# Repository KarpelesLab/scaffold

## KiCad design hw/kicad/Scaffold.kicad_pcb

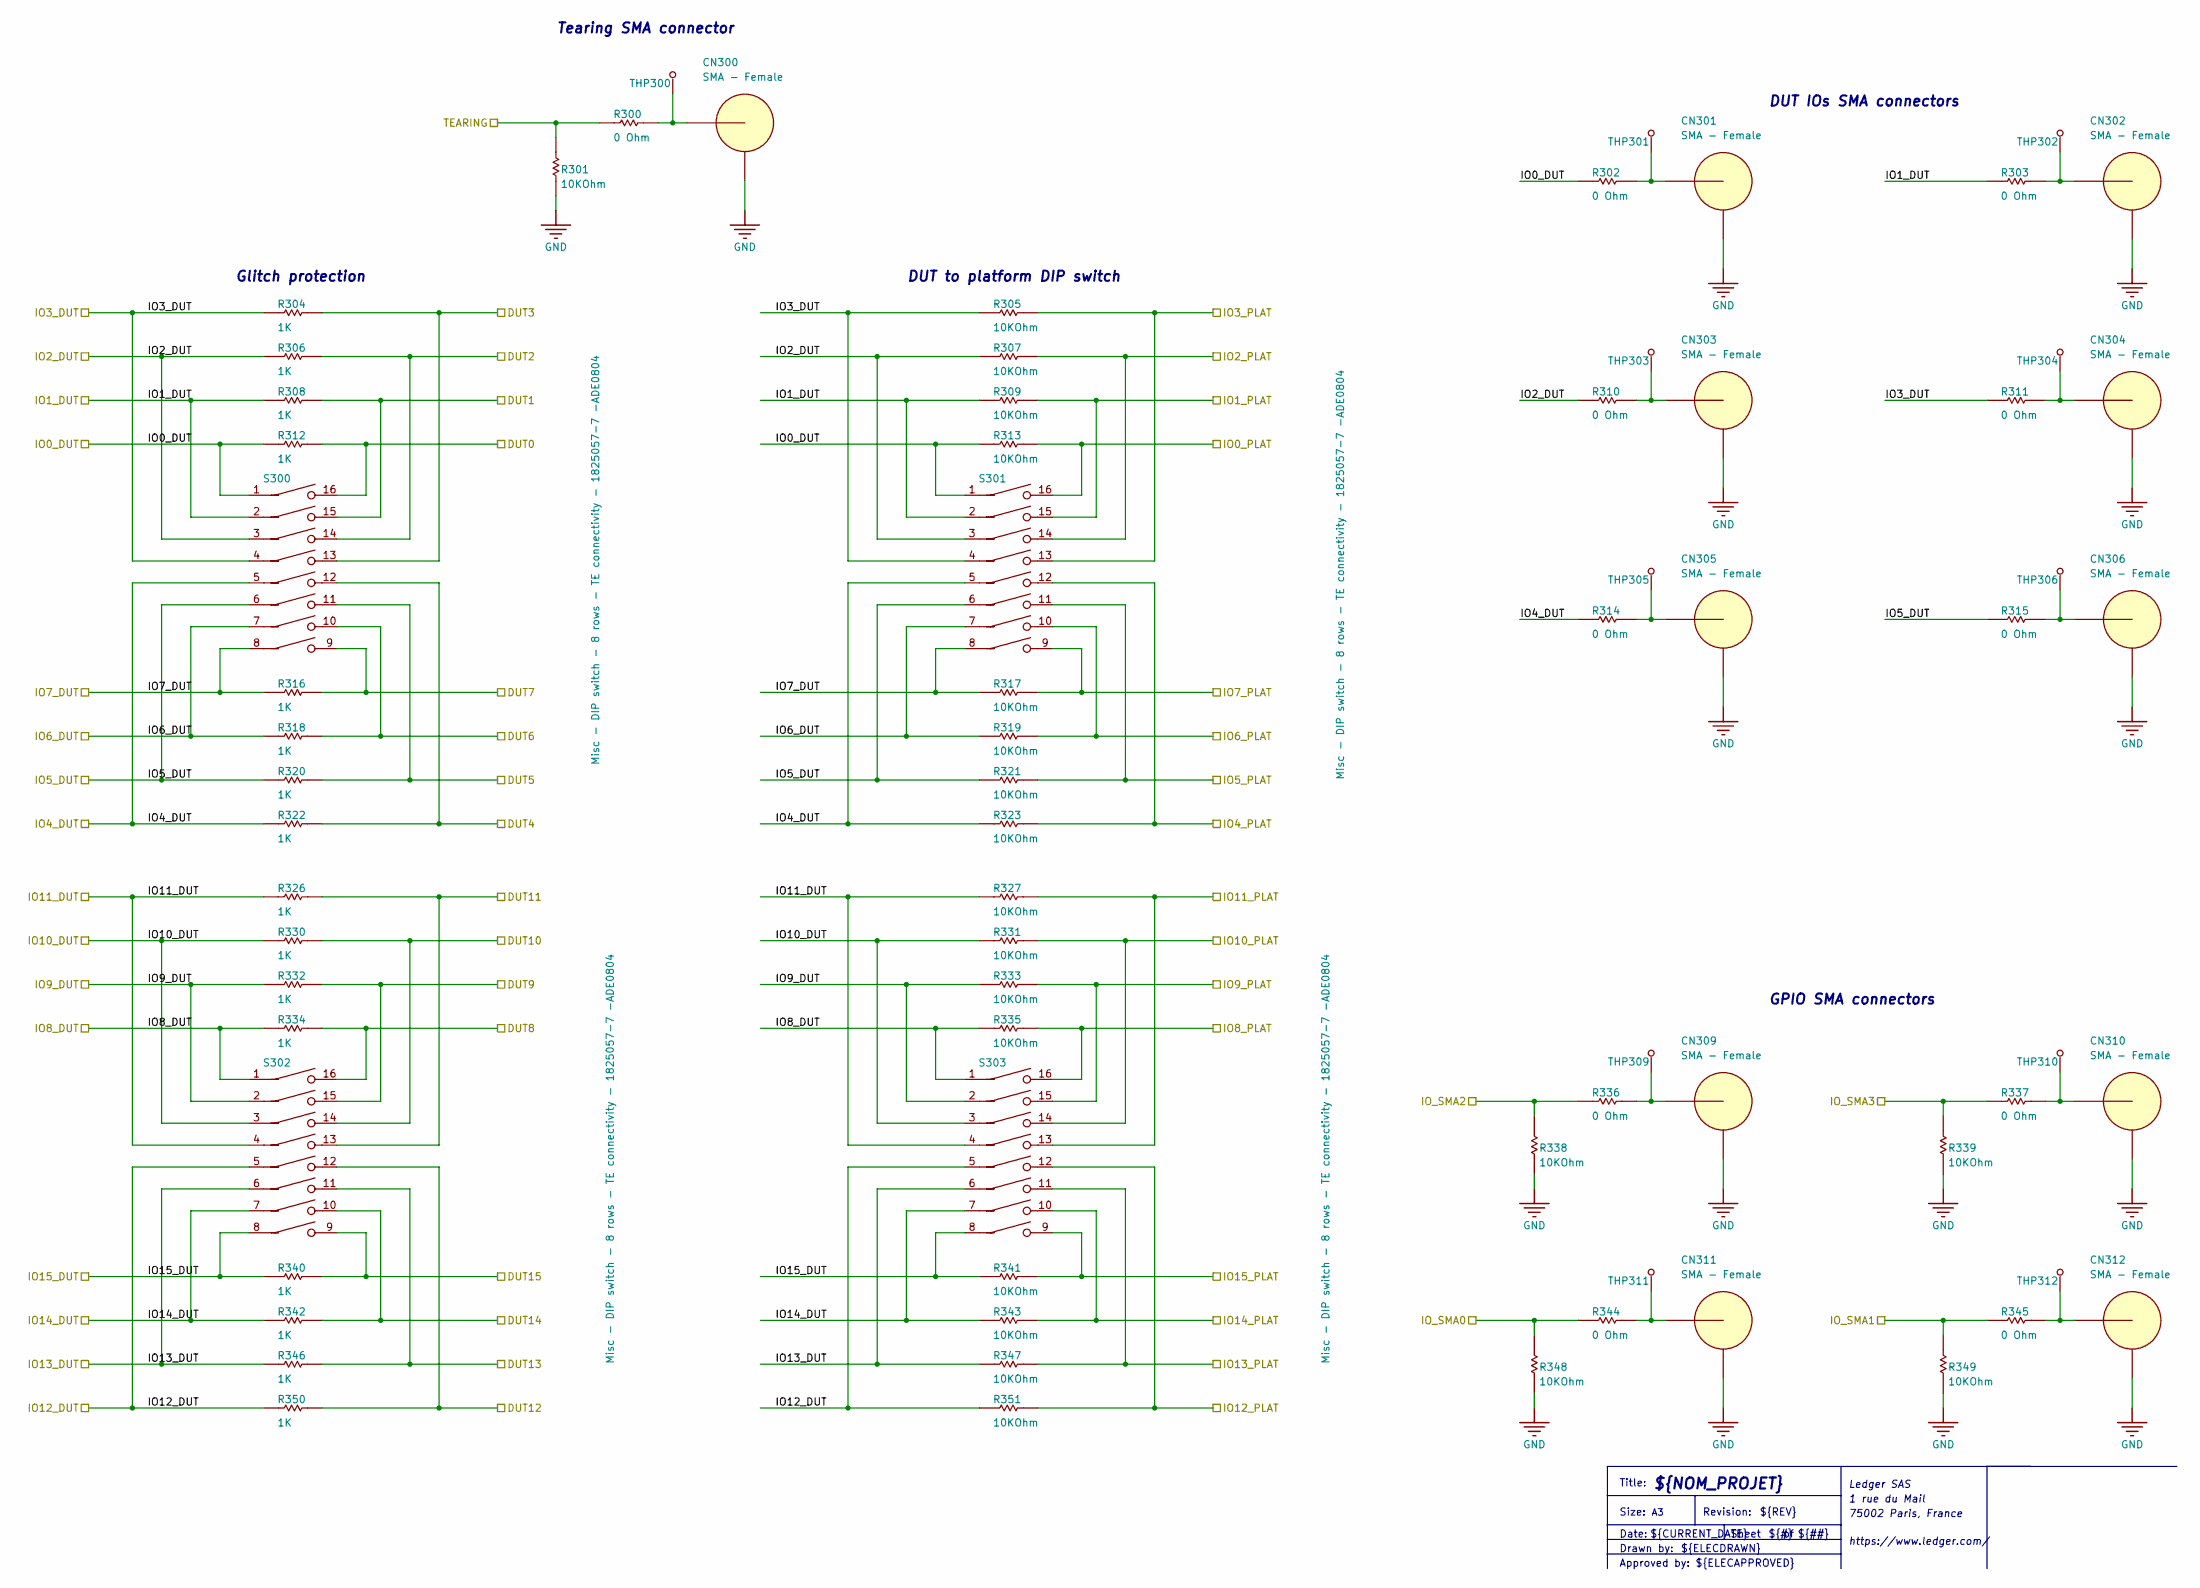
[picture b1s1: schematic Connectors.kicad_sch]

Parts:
CN300, CN301, CN302, CN303, CN304, CN305, CN306, CN309, CN310, CN311, CN312: SMA - Female; SAMTEC_SMA-J-P-X-ST-EM3; MANUFACTURER PN SMA–J–P–H–ST–EM3
R300, R302, R303, R310, R311, R314, R315, R336, R337, R344, R345: 0 Ohm; RES0603; TOLERANCE 1%; MANUFACTURER PN CRCW06030000FKEA
R301, R305, R307, R309, R313, R317, R319, R321, R323, R327, R331, R333, R335, R338, R339, R341, R343, R347, R348, R349, R351: 10KOhm; RES0603; TOLERANCE 1%; MANUFACTURER PN RC0603FR-0710KL
R304, R306, R308, R312, R316, R318, R320, R322, R326, R330, R332, R334, R340, R342, R346, R350: 1K; RES0603; TOLERANCE 1%; MANUFACTURER PN RC0603FR-071KL
S300, S301, S302, S303: Misc - DIP switch - 8 rows - TE connectivity - 18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; SWDIP16_300X3.51; MANUFACTURER PN1 ADE0804
THP300, THP301, THP302, THP303, THP304, THP305, THP306, THP309, THP310, THP311, THP312: Misc - Test pin - Through hole - Millmax - 6821-0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; MILLMAX_6821-0-00-15-00-00-08-0; MANUFACTURER PN 6821-0-00-15-00-00-08-0

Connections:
/DUT_D0: R312.2, S300.16; also elsewhere on the board
/DUT_D1: R308.2, S300.15; also elsewhere on the board
/DUT_D2: R306.2, S300.14; also elsewhere on the board
/U_Connectors/DUT3: R304.2, S300.13; also elsewhere on the board
/U_Connectors/DUT4: R322.2, S300.12; also elsewhere on the board
/U_Connectors/DUT5: R320.2, S300.11; also elsewhere on the board
/U_Connectors/DUT6: R318.2, S300.10; also elsewhere on the board
/U_Connectors/DUT7: R316.2, S300.9; also elsewhere on the board
/U_Connectors/DUT8: R334.2, S302.16; also elsewhere on the board
/U_Connectors/DUT9: R332.2, S302.15; also elsewhere on the board
/U_Connectors/DUT10: R330.2, S302.14; also elsewhere on the board
/U_Connectors/DUT11: R326.2, S302.13; also elsewhere on the board
/U_Connectors/DUT12: R350.2, S302.12; also elsewhere on the board
/U_Connectors/DUT13: R346.2, S302.11; also elsewhere on the board
/U_Connectors/DUT14: R342.2, S302.10; also elsewhere on the board
/U_Connectors/DUT15: R340.2, S302.9; also elsewhere on the board
/U_Connectors/IO0_DUT: R302.1, R312.1, R313.1, S300.1, S301.1; also elsewhere on the board
/U_Connectors/IO0_PLAT: R313.2, S301.16; also elsewhere on the board
/U_Connectors/IO1_DUT: R303.1, R308.1, R309.1, S300.2, S301.2; also elsewhere on the board
/U_Connectors/IO1_PLAT: R309.2, S301.15; also elsewhere on the board
/U_Connectors/IO2_DUT: R306.1, R307.1, R310.1, S300.3, S301.3; also elsewhere on the board
/U_Connectors/IO2_PLAT: R307.2, S301.14; also elsewhere on the board
/U_Connectors/IO3_DUT: R304.1, R305.1, R311.1, S300.4, S301.4; also elsewhere on the board
/U_Connectors/IO3_PLAT: R305.2, S301.13; also elsewhere on the board
/U_Connectors/IO4_DUT: R314.1, R322.1, R323.1, S300.5, S301.5; also elsewhere on the board
/U_Connectors/IO4_PLAT: R323.2, S301.12; also elsewhere on the board
/U_Connectors/IO5_DUT: R315.1, R320.1, R321.1, S300.6, S301.6; also elsewhere on the board
/U_Connectors/IO5_PLAT: R321.2, S301.11; also elsewhere on the board
/U_Connectors/IO6_DUT: R318.1, R319.1, S300.7, S301.7; also elsewhere on the board
/U_Connectors/IO6_PLAT: R319.2, S301.10; also elsewhere on the board
/U_Connectors/IO7_DUT: R316.1, R317.1, S300.8, S301.8; also elsewhere on the board
/U_Connectors/IO7_PLAT: R317.2, S301.9; also elsewhere on the board
/U_Connectors/IO8_DUT: R334.1, R335.1, S302.1, S303.1; also elsewhere on the board
/U_Connectors/IO8_PLAT: R335.2, S303.16; also elsewhere on the board
/U_Connectors/IO9_DUT: R332.1, R333.1, S302.2, S303.2; also elsewhere on the board
/U_Connectors/IO9_PLAT: R333.2, S303.15; also elsewhere on the board
/U_Connectors/IO10_DUT: R330.1, R331.1, S302.3, S303.3; also elsewhere on the board
/U_Connectors/IO10_PLAT: R331.2, S303.14; also elsewhere on the board
/U_Connectors/IO11_DUT: R326.1, R327.1, S302.4, S303.4; also elsewhere on the board
/U_Connectors/IO11_PLAT: R327.2, S303.13; also elsewhere on the board
/U_Connectors/IO12_DUT: R350.1, R351.1, S302.5, S303.5; also elsewhere on the board
/U_Connectors/IO12_PLAT: R351.2, S303.12; also elsewhere on the board
/U_Connectors/IO13_DUT: R346.1, R347.1, S302.6, S303.6; also elsewhere on the board
/U_Connectors/IO13_PLAT: R347.2, S303.11; also elsewhere on the board
/U_Connectors/IO14_DUT: R342.1, R343.1, S302.7, S303.7; also elsewhere on the board
/U_Connectors/IO14_PLAT: R343.2, S303.10; also elsewhere on the board
/U_Connectors/IO15_DUT: R340.1, R341.1, S302.8, S303.8; also elsewhere on the board
/U_Connectors/IO15_PLAT: R341.2, S303.9; also elsewhere on the board
/U_Connectors/IO_SMA0: R344.1, R348.2; also elsewhere on the board
/U_Connectors/IO_SMA1: R345.1, R349.2; also elsewhere on the board
/U_Connectors/IO_SMA2: R336.1, R338.2; also elsewhere on the board
/U_Connectors/IO_SMA3: R337.1, R339.2; also elsewhere on the board
/U_Connectors/TEARING: R300.1, R301.2; also elsewhere on the board
GND: CN300.2, CN300.3, CN301.2, CN301.3, CN302.2, CN302.3, CN303.2, CN303.3, CN304.2, CN304.3, CN305.2, CN305.3, CN306.2, CN306.3, CN309.2, CN309.3, CN310.2, CN310.3, CN311.2, CN311.3, CN312.2, CN312.3, R301.1, R338.1, R339.1, R348.1, R349.1; also elsewhere on the board
unnamed: CN300.1, R300.2, THP300.1
unnamed: CN301.1, R302.2, THP301.1
unnamed: CN302.1, R303.2, THP302.1
unnamed: CN303.1, R310.2, THP303.1
unnamed: CN304.1, R311.2, THP304.1
unnamed: CN305.1, R314.2, THP305.1
unnamed: CN306.1, R315.2, THP306.1
unnamed: CN309.1, R336.2, THP309.1
unnamed: CN310.1, R337.2, THP310.1
unnamed: CN311.1, R344.2, THP311.1
unnamed: CN312.1, R345.2, THP312.1

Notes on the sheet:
Sheet
DUT IOs SMA connectors
Drawn by:
Tearing SMA connector
GPIO SMA connectors
Glitch protection
${ELECDRAWN}
Ledger SAS
${REV}
${CURRENT_DATE}
https://www.ledger.com/
Revision:
Title:
1 rue du Mail
Approved by:
DUT to platform DIP switch
${NOM_PROJET}
Size:
${##}
Date:
${#}
${ELECAPPROVED}
75002 Paris, France

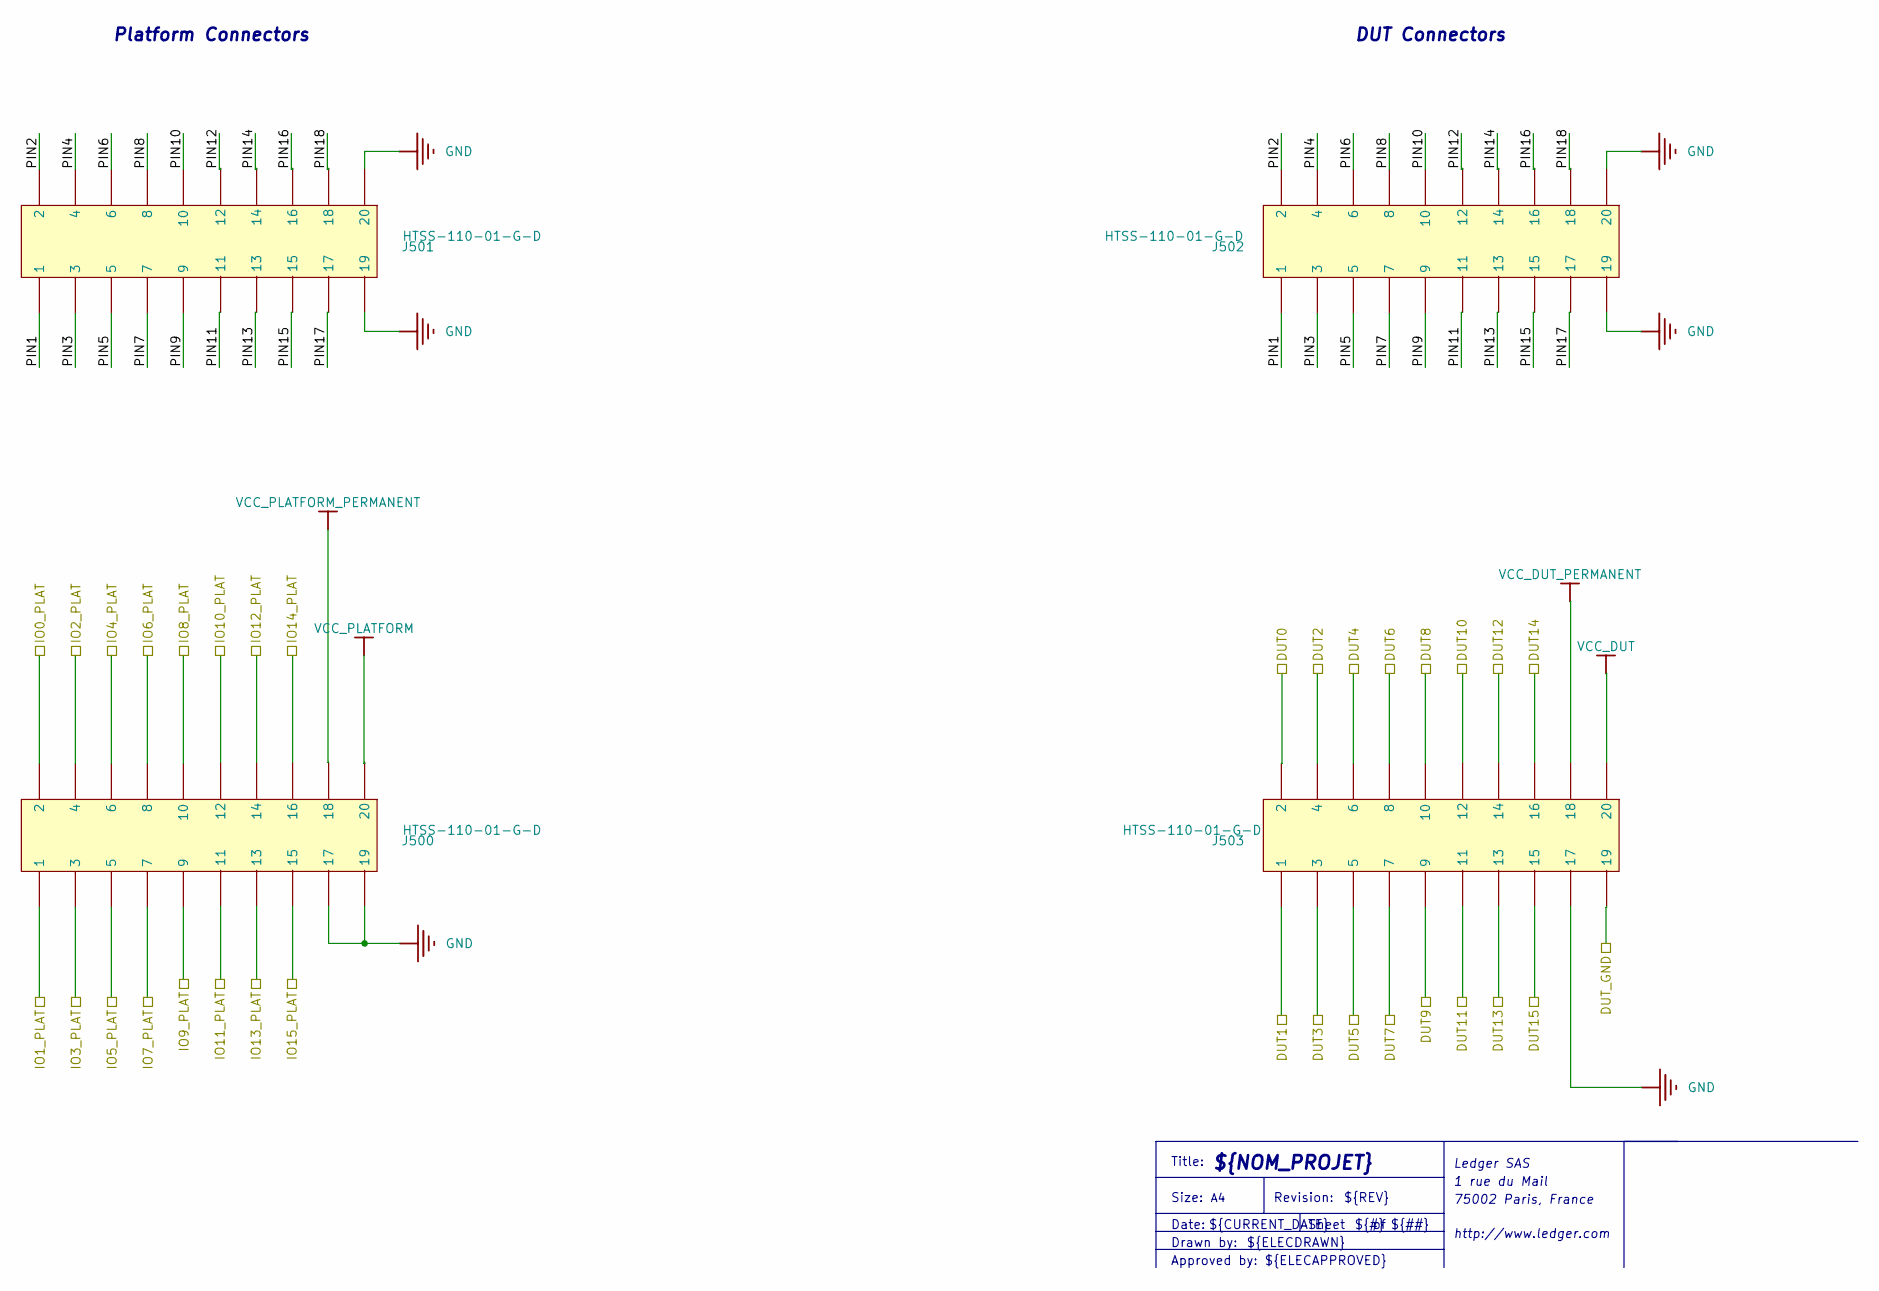
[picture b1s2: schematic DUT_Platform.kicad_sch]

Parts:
J500, J501, J502, J503: HTSS-110-01-G-D; SAMTEC_HTSS-110-01-G-D; MANUFACTURER PN HTSS-110-01-G-D

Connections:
/DUT_D0: J503.2; also elsewhere on the board
/DUT_D1: J503.1; also elsewhere on the board
/DUT_D2: J503.4; also elsewhere on the board
/U_Connectors/DUT3: J503.3; also elsewhere on the board
/U_Connectors/DUT4: J503.6; also elsewhere on the board
/U_Connectors/DUT5: J503.5; also elsewhere on the board
/U_Connectors/DUT6: J503.8; also elsewhere on the board
/U_Connectors/DUT7: J503.7; also elsewhere on the board
/U_Connectors/DUT8: J503.10; also elsewhere on the board
/U_Connectors/DUT9: J503.9; also elsewhere on the board
/U_Connectors/DUT10: J503.12; also elsewhere on the board
/U_Connectors/DUT11: J503.11; also elsewhere on the board
/U_Connectors/DUT12: J503.14; also elsewhere on the board
/U_Connectors/DUT13: J503.13; also elsewhere on the board
/U_Connectors/DUT14: J503.16; also elsewhere on the board
/U_Connectors/DUT15: J503.15; also elsewhere on the board
/U_Connectors/IO0_PLAT: J500.2; also elsewhere on the board
/U_Connectors/IO1_PLAT: J500.1; also elsewhere on the board
/U_Connectors/IO2_PLAT: J500.4; also elsewhere on the board
/U_Connectors/IO3_PLAT: J500.3; also elsewhere on the board
/U_Connectors/IO4_PLAT: J500.6; also elsewhere on the board
/U_Connectors/IO5_PLAT: J500.5; also elsewhere on the board
/U_Connectors/IO6_PLAT: J500.8; also elsewhere on the board
/U_Connectors/IO7_PLAT: J500.7; also elsewhere on the board
/U_Connectors/IO8_PLAT: J500.10; also elsewhere on the board
/U_Connectors/IO9_PLAT: J500.9; also elsewhere on the board
/U_Connectors/IO10_PLAT: J500.12; also elsewhere on the board
/U_Connectors/IO11_PLAT: J500.11; also elsewhere on the board
/U_Connectors/IO12_PLAT: J500.14; also elsewhere on the board
/U_Connectors/IO13_PLAT: J500.13; also elsewhere on the board
/U_Connectors/IO14_PLAT: J500.16; also elsewhere on the board
/U_Connectors/IO15_PLAT: J500.15; also elsewhere on the board
/U_DUT_Platform/DUT_GND: J503.19; also elsewhere on the board
/U_DUT_Platform/PIN1: J501.1, J502.1
/U_DUT_Platform/PIN2: J501.2, J502.2
/U_DUT_Platform/PIN3: J501.3, J502.3
/U_DUT_Platform/PIN4: J501.4, J502.4
/U_DUT_Platform/PIN5: J501.5, J502.5
/U_DUT_Platform/PIN6: J501.6, J502.6
/U_DUT_Platform/PIN7: J501.7, J502.7
/U_DUT_Platform/PIN8: J501.8, J502.8
/U_DUT_Platform/PIN9: J501.9, J502.9
/U_DUT_Platform/PIN10: J501.10, J502.10
/U_DUT_Platform/PIN11: J501.11, J502.11
/U_DUT_Platform/PIN12: J501.12, J502.12
/U_DUT_Platform/PIN13: J501.13, J502.13
/U_DUT_Platform/PIN14: J501.14, J502.14
/U_DUT_Platform/PIN15: J501.15, J502.15
/U_DUT_Platform/PIN16: J501.16, J502.16
/U_DUT_Platform/PIN17: J501.17, J502.17
/U_DUT_Platform/PIN18: J501.18, J502.18
GND: J500.17, J500.19, J501.19, J501.20, J502.19, J502.20, J503.17; also elsewhere on the board
VCC_DUT: J503.20; also elsewhere on the board
VCC_DUT_PERMANENT: J503.18; also elsewhere on the board
VCC_PLATFORM: J500.20; also elsewhere on the board
VCC_PLATFORM_PERMANENT: J500.18; also elsewhere on the board

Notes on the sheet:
${NOM_PROJET}
${#}
DUT Connectors
Sheet
Revision:
Drawn by:
${ELECAPPROVED}
${REV}
http://www.ledger.com
${##}
75002 Paris, France
1 rue du Mail
${ELECDRAWN}
Ledger SAS
Date:
${CURRENT_DATE}
Approved by:
Title:
Size:
Platform Connectors

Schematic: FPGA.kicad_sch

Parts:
C100, C101: 100uF 6.3V; C_1206_3216Metric; LCSC C15008
C102, C103, C104, C105, C106, C107, C119, C120, C127, C128, C129, C130, C131, C158, C159, C160, C161: 4.7uF 10V; C_0402_1005Metric; LCSC C23733
C108, C109, C110, C111, C112, C113, C114, C115, C116, C117, C121, C122, C123, C124, C132, C133, C134, C135, C143, C144, C145, C146, C155, C156, C162, C163, C164, C165, C166, C167, C168, C169: 470nF 10V; C_0402_1005Metric; LCSC C47339
C118, C125, C126, C157: 47uF 6.3V; C_0805_2012Metric; LCSC C16780
C136: 100nF; CAP0603; TOLERANCE 10%; MANUFACTURER PN 885012206046
C137: 10uF; CAP0603; TOLERANCE 20%; MANUFACTURER PN GRM188R61C106MA73D
C151, C153, C154: 100nF; CAP0603; TOLERANCE 10%; MANUFACTURER2 PN MCCA000159
C170: 1uF 50V; C_0603_1608Metric; LCSC C15849
C171: 100nF 50V; C_0603_1608Metric; LCSC C14663
CN100: SMA - Female; SAMTEC_SMA-J-P-X-ST-EM3; MANUFACTURER PN SMA–J–P–H–ST–EM3
L100: 600R@100MHz; L_0603_1608Metric; LCSC C1002
P100: JTAG; PinHeader_1x06_P2.54mm_Vertical; MANUFACTURER PN PZ254V-11-06P; LCSC C492405
R100: 47KOhm; RES0603; TOLERANCE 1%; MANUFACTURER PN RC0603FR-0747KL
R101, R102, R103: 10k; R_0603_1608Metric; LCSC C25804
R104, R105: 4.7k; R_0603_1608Metric; LCSC C23162
R106: 330; R_0603_1608Metric; LCSC C23138
R107, R108, R109, R113: 1k; R_0603_1608Metric; LCSC C21190
R110, R111, R112: 10KOhm; RES0603; TOLERANCE 1%; MANUFACTURER PN RC0603FR-0710KL
S100: Misc - Button - WURTH 430152080826; 430152080826; RATED VOLTAGE 12 VDC; MANUFACTURER PN 430152080826
TCK100: TP; TP_001
TDI100: TP; TP_001
TDO100: TP; TP_001
TMS100: TP; TP_001
TP100, TP101, TP102, TP103, TP104, TP105, TP106, TP107, TP108, TP111: TP; TP_001
U100: XC7A35T-1CSG324I; Xilinx_CSG324; MANUFACTURER PN XC7A35T-1CSG324I; LCSC C1521726
U105: W25Q128JVSIQ; SOIC-8_5.3x5.3mm_P1.27mm; MANUFACTURER PN W25Q128JVSIQ; LCSC C97521
Y100: Oscillator - 25MHz - 3.3V - HCMOS - ECS-2520S33-2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; XTAL_2520; MANUFACTURER PN ECS-2520S33-250-FN-TR; LCSC C2441341

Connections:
1V0: C100.1, C101.1, C102.1, C103.1, C104.1, C105.1, C106.1, C107.1, C108.1, C109.1, C110.1, C111.1, C112.1, C113.1, C114.1, C115.1, C116.1, C117.1, U100.F8 (VCCINT), U100.F10 (VCCBRAM), U100.G7 (VCCINT), U100.G9 (VCCINT), U100.G11 (VCCBRAM), U100.H8 (VCCINT), U100.J7 (VCCINT), U100.J11 (VCCINT), U100.K8 (VCCINT), U100.L7 (VCCINT), U100.L11 (VCCINT), U100.M8 (VCCINT), U100.M10 (VCCINT), U100.N7 (VCCINT), U100.N9 (VCCINT), U100.N11 (VCCINT); also elsewhere on the board
1V8: C118.1, C119.1, C120.1, C121.1, C122.1, C123.1, C124.1, L100.1, U100.F12 (VCCAUX), U100.H12 (VCCAUX), U100.K12 (VCCAUX), U100.M12 (VCCAUX); also elsewhere on the board
3V3_FPGA: C125.1, C126.1, C127.1, C128.1, C129.1, C130.1, C131.1, C132.1, C133.1, C134.1, C135.1, C136.1, C143.1, C144.1, C145.1, C146.1, C151.2, C153.2, C154.2, C155.1, C156.1, P100.1, R100.2, R101.1, R102.1, R103.1, R104.1, R105.1, R106.1, R107.1, R113.1, U100.A17 (VCCO_15), U100.B10 (VCCO_16), U100.C13 (VCCO_15), U100.D16 (VCCO_15), U100.G15 (VCCO_15), U100.H18 (VCCO_15), U100.K14 (VCCO_15), U100.L17 (VCCO_14), U100.N13 (VCCO_14), U100.P8 (CFGBVS_0), U100.P16 (VCCO_14), U100.R9 (VCCO_0), U100.T12 (VCCO_14), U100.U15 (VCCO_14), U100.V18 (VCCO_14), U105.8 (VCC), Y100.1 (EN), Y100.4 (VDD); also elsewhere on the board
/DUT_D0: R110.2; also elsewhere on the board
/DUT_D1: R111.2; also elsewhere on the board
/DUT_D2: R112.1; also elsewhere on the board
/U_Connectors/IO0_DUT: U100.A1 (IO_L9N_T1_DQS_AD7N_35); also elsewhere on the board
/U_Connectors/IO0_PLAT: U100.L1 (IO_L1P_T0_34); also elsewhere on the board
/U_Connectors/IO1_DUT: U100.A3 (IO_L8N_T1_AD14N_35); also elsewhere on the board
/U_Connectors/IO1_PLAT: U100.M1 (IO_L1N_T0_34); also elsewhere on the board
/U_Connectors/IO2_DUT: U100.A4 (IO_L8P_T1_AD14P_35); also elsewhere on the board
/U_Connectors/IO2_PLAT: U100.N1 (IO_L3N_T0_DQS_34); also elsewhere on the board
/U_Connectors/IO3_DUT: U100.A5 (IO_L3N_T0_DQS_AD5N_35); also elsewhere on the board
/U_Connectors/IO3_PLAT: U100.R1 (IO_L17P_T2_34); also elsewhere on the board
/U_Connectors/IO4_DUT: U100.A6 (IO_L3P_T0_DQS_AD5P_35); also elsewhere on the board
/U_Connectors/IO4_PLAT: U100.T1 (IO_L17N_T2_34); also elsewhere on the board
/U_Connectors/IO5_DUT: U100.B1 (IO_L9P_T1_DQS_AD7P_35); also elsewhere on the board
/U_Connectors/IO5_PLAT: U100.U1 (IO_L7P_T1_34); also elsewhere on the board
/U_Connectors/IO6_DUT: U100.C1 (IO_L16N_T2_35); also elsewhere on the board
/U_Connectors/IO6_PLAT: U100.V1 (IO_L7N_T1_34); also elsewhere on the board
/U_Connectors/IO7_DUT: U100.E1 (IO_L18N_T2_35); also elsewhere on the board
/U_Connectors/IO7_PLAT: U100.V2 (IO_L9N_T1_DQS_34); also elsewhere on the board
/U_Connectors/IO8_DUT: U100.F1 (IO_L18P_T2_35); also elsewhere on the board
/U_Connectors/IO8_PLAT: U100.V4 (IO_L10N_T1_34); also elsewhere on the board
/U_Connectors/IO9_DUT: U100.G1 (IO_L17N_T2_35); also elsewhere on the board
/U_Connectors/IO9_PLAT: U100.V5 (IO_L10P_T1_34); also elsewhere on the board
/U_Connectors/IO10_DUT: U100.H1 (IO_L17P_T2_35); also elsewhere on the board
/U_Connectors/IO10_PLAT: U100.V6 (IO_L20N_T3_34); also elsewhere on the board
/U_Connectors/IO11_DUT: U100.K1 (IO_L23N_T3_35); also elsewhere on the board
/U_Connectors/IO11_PLAT: U100.V7 (IO_L20P_T3_34); also elsewhere on the board
/U_Connectors/IO12_DUT: U100.B2 (IO_L10N_T1_AD15N_35); also elsewhere on the board
/U_Connectors/IO12_PLAT: U100.V9 (IO_L21N_T3_DQS_34); also elsewhere on the board
/U_Connectors/IO13_DUT: U100.B3 (IO_L10P_T1_AD15P_35); also elsewhere on the board
/U_Connectors/IO13_PLAT: U100.M2 (IO_L4N_T0_34); also elsewhere on the board
/U_Connectors/IO14_DUT: U100.B4 (IO_L7N_T1_AD6N_35); also elsewhere on the board
/U_Connectors/IO14_PLAT: U100.N2 (IO_L3P_T0_DQS_34); also elsewhere on the board
/U_Connectors/IO15_DUT: U100.B6 (IO_L2N_T0_AD12N_35); also elsewhere on the board
/U_Connectors/IO15_PLAT: U100.P2 (IO_L15P_T2_DQS_34); also elsewhere on the board
/U_Connectors/TEARING: U100.B13 (IO_L2P_T0_AD8P_15); also elsewhere on the board
/U_FPGA/CLK_25M: TP101.1, U100.C15 (IO_L12N_T1_MRCC_15), Y100.3 (OUT)
/U_FPGA/CLK_EXT: CN100.1, U100.G16 (IO_L13N_T2_MRCC_15)
/U_FPGA/DIR_A0: U100.G18 (IO_L22P_T3_A17_15); also elsewhere on the board
/U_FPGA/DIR_A1: U100.J18 (IO_L23N_T3_FWE_B_15); also elsewhere on the board
/U_FPGA/DIR_A2: U100.B11 (IO_L4P_T0_15); also elsewhere on the board
/U_FPGA/DIR_A3: U100.B12 (IO_L3N_T0_DQS_AD1N_15); also elsewhere on the board
/U_FPGA/DONE: R106.2, U100.P10 (DONE_0)
/U_FPGA/EN_VCC_DUT: U100.B16 (IO_L7P_T1_AD2P_15); also elsewhere on the board
/U_FPGA/EN_VCC_PLATFORM: U100.B14 (IO_L2N_T0_AD8N_15); also elsewhere on the board
/U_FPGA/FLASH_CLK: U100.E9 (CCLK_0), U105.6 (CLK)
/U_FPGA/FLASH_CS: R101.2, U100.L13 (IO_L6P_T0_FCS_B_14), U105.1 (~CS)
/U_FPGA/FLASH_IO0: U100.K17 (IO_L1P_T0_D00_MOSI_14), U105.5 (DI/IO_{0})
/U_FPGA/FLASH_IO1: U100.K18 (IO_L1N_T0_D01_DIN_14), U105.2 (DO/IO_{1})
/U_FPGA/FLASH_IO2: R102.2, U100.L14 (IO_L2P_T0_D02_14), U105.3 (~WP/IO_{2})
/U_FPGA/FLASH_IO3: R103.2, U100.M14 (IO_L2N_T0_D03_14), U105.7 (~HOLD/~RESET/IO_{3})
/U_FPGA/INIT_B: R105.2, TP111.1, U100.P7 (INIT_B_0)
/U_FPGA/IO_A0: U100.B18 (IO_L10P_T1_AD11P_15); also elsewhere on the board
/U_FPGA/IO_A1: U100.D18 (IO_L21N_T3_DQS_A18_15); also elsewhere on the board
/U_FPGA/IO_A2: U100.E18 (IO_L21P_T3_DQS_15); also elsewhere on the board
/U_FPGA/IO_A3: U100.F18 (IO_L22N_T3_A16_15); also elsewhere on the board
/U_FPGA/JTAG_TCK: P100.3, TCK100.1, U100.E10 (TCK_0)
/U_FPGA/JTAG_TDI: P100.5, TDI100.1, U100.E11 (TDI_0)
/U_FPGA/JTAG_TDO: P100.4, TDO100.1, U100.E13 (TDO_0)
/U_FPGA/JTAG_TMS: P100.6, TMS100.1, U100.E12 (TMS_0)
/U_FPGA/LED_CLK: U100.A13 (IO_L9P_T1_DQS_AD3P_15); also elsewhere on the board
/U_FPGA/LED_LE: U100.A14 (IO_L9N_T1_DQS_AD3N_15); also elsewhere on the board
/U_FPGA/LED_SDI: U100.A15 (IO_L8P_T1_AD10P_15); also elsewhere on the board
/U_FPGA/LED_SDO: U100.A16 (IO_L8N_T1_AD10N_15); also elsewhere on the board
/U_FPGA/LED_/OE: U100.A18 (IO_L10N_T1_AD11N_15); also elsewhere on the board
/U_FPGA/MODE_M0: R107.2, U100.P12 (M0_0)
/U_FPGA/MODE_M1: R108.1, U100.P13 (M1_0)
/U_FPGA/MODE_M2: R109.1, U100.P11 (M2_0)
/U_FPGA/PROGRAM_B: R104.2, U100.P9 (PROGRAM_B_0)
/U_FPGA/PUDC_B: R113.2, U100.L15 (IO_L3P_T0_DQS_PUDC_B_14)
/U_FPGA/PULL_D0: R110.1, U100.B7 (IO_L2P_T0_AD12P_35)
/U_FPGA/PULL_D1: R111.1, U100.C2 (IO_L16P_T2_35)
/U_FPGA/PULL_D2: R112.2, U100.D2 (IO_L14N_T2_SRCC_35)
/U_FPGA/RESET_N: C137.2, R100.1, S100.1, S100.3, TP100.1, U100.A11 (IO_L4N_T0_15)
/U_FPGA/RXD: U100.M18 (IO_L4N_T0_D05_14); also elsewhere on the board
/U_FPGA/SPARE_0: TP102.1, U100.T18 (IO_L7N_T1_D10_14)
/U_FPGA/SPARE_1: TP103.1, U100.U18 (IO_L17N_T2_A13_D29_14)
/U_FPGA/SPARE_2: TP104.1, U100.V10 (IO_L21P_T3_DQS_14)
/U_FPGA/SPARE_3: TP105.1, U100.V11 (IO_L21N_T3_DQS_A06_D22_14)
/U_FPGA/SPARE_4: TP106.1, U100.V12 (IO_L20N_T3_A07_D23_14)
/U_FPGA/SPARE_5: TP107.1, U100.V14 (IO_L22N_T3_A04_D20_14)
/U_FPGA/SPARE_6: TP108.1, U100.V15 (IO_L16P_T2_CSI_B_14)
/U_FPGA/TXD: U100.L18 (IO_L4P_T0_D04_14); also elsewhere on the board
GND: C100.2, C101.2, C102.2, C103.2, C104.2, C105.2, C106.2, C107.2, C108.2, C109.2, C110.2, C111.2, C112.2, C113.2, C114.2, C115.2, C116.2, C117.2, C118.2, C119.2, C120.2, C121.2, C122.2, C123.2, C124.2, C125.2, C126.2, C127.2, C128.2, C129.2, C130.2, C131.2, C132.2, C133.2, C134.2, C135.2, C136.2, C137.1, C143.2, C144.2, C145.2, C146.2, C151.1, C153.1, C154.1, C155.2, C156.2, C157.2, C158.2, C159.2, C160.2, C161.2, C162.2, C163.2, C164.2, C165.2, C166.2, C167.2, C168.2, C169.2, C170.2, C171.2, CN100.2, CN100.3, P100.2, R108.2, R109.2, S100.2, S100.4, U100.A2 (GND), U100.A12 (GND), U100.B5 (GND), U100.B15 (GND), U100.C8 (GND), U100.C18 (GND), U100.D1 (GND), U100.D11 (GND), U100.E4 (GND), U100.E8 (VCCBATT_0), U100.E14 (GND), U100.F7 (GND), U100.F9 (GND), U100.F11 (GND), U100.F17 (GND), U100.G8 (GND), U100.G10 (GND), U100.G12 (GND), U100.H3 (GND), U100.H7 (GND), U100.H9 (GNDADC_0), U100.H11 (GND), U100.H13 (GND), U100.J6 (GND), U100.J8 (GND), U100.J9 (VREFN_0), U100.J10 (VP_0), U100.J12 (GND), U100.J16 (GND), U100.K7 (GND), U100.K9 (VN_0), U100.K10 (VREFP_0), U100.K11 (GND), U100.L2 (GND), U100.L8 (GND), U100.L9 (DXN_0), U100.L10 (DXP_0), U100.L12 (GND), U100.M5 (GND), U100.M7 (GND), U100.M9 (GND), U100.M11 (GND), U100.M15 (GND), U100.N8 (GND), U100.N10 (GND), U100.N12 (GND), U100.N18 (GND), U100.P1 (GND), U100.R4 (GND), U100.R14 (GND), U100.T7 (GND), U100.T17 (GND), U100.U10 (GND), U100.V3 (GND), U100.V13 (GND), U105.4 (GND), Y100.2 (GND); also elsewhere on the board
PD_SCL: U100.P18 (IO_L9N_T1_DQS_D13_14); also elsewhere on the board
PD_SDA: U100.R18 (IO_L7P_T1_D09_14); also elsewhere on the board
VCCADC: C170.1, C171.1, L100.2, U100.H10 (VCCADC_0)
VCC_IO_FPGA: C157.1, C158.1, C159.1, C160.1, C161.1, C162.1, C163.1, C164.1, C165.1, C166.1, C167.1, C168.1, C169.1, U100.A7 (VCCO_35), U100.C3 (VCCO_35), U100.D6 (VCCO_35), U100.F2 (VCCO_35), U100.G5 (VCCO_35), U100.J1 (VCCO_35), U100.K4 (VCCO_34), U100.N3 (VCCO_34), U100.P6 (VCCO_34), U100.T2 (VCCO_34), U100.U5 (VCCO_34), U100.V8 (VCCO_34); also elsewhere on the board

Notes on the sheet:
U100 Banks 14 and 15 (3V3_FPGA)
U100 Bank 34 (VCC_IO_FPGA), VCCO_16
U100 Bank 35 (VCC_IO_FPGA)
U100 Bank 0: configuration and JTAG
U100 Power
Configuration: Master SPI x4 (M[2:0] = 001), W25Q128JV
JTAG (Digilent JTAG-HS2/HS3 6-pin header: VDD GND TCK TDO TDI TMS)
Clocks and reset
D0-D2 pull resistors, spare I/O test points
Decoupling (UG483 Table 2-2, sized for XC7A100T)
